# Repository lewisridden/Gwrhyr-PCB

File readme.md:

# PCB for Gwrhyr 
The flex PCB for Gwrhyr is forked from an improved variant of the BastardKB open-source manuform board, including the improvements for shape and access made by crystalhand.

The board has been modified in the following ways:
- Key footprints changed to Choc switches using the [reversible footprint by Keebio](https://github.com/keebio/Keebio-Parts.pretty/blob/master/Kailh-PG1350-1u-No-Clickhole.kicad_mod)
- Updated diode footprint to one from above Keebio library 
- Added HAT thumb cluster board
- Added board mount derived from [Swanmatch's ProMicro-Home](https://github.com/swanmatch/MxLEDBitPCB/tree/master/MxLEDBitPCB-promicro)

## License (inherited from fork)

Licensed under CC BY-NC-SA 4.0
Copyright Quentin Lebastard, Crystalhand, Swanmatch, Lewis Merriman

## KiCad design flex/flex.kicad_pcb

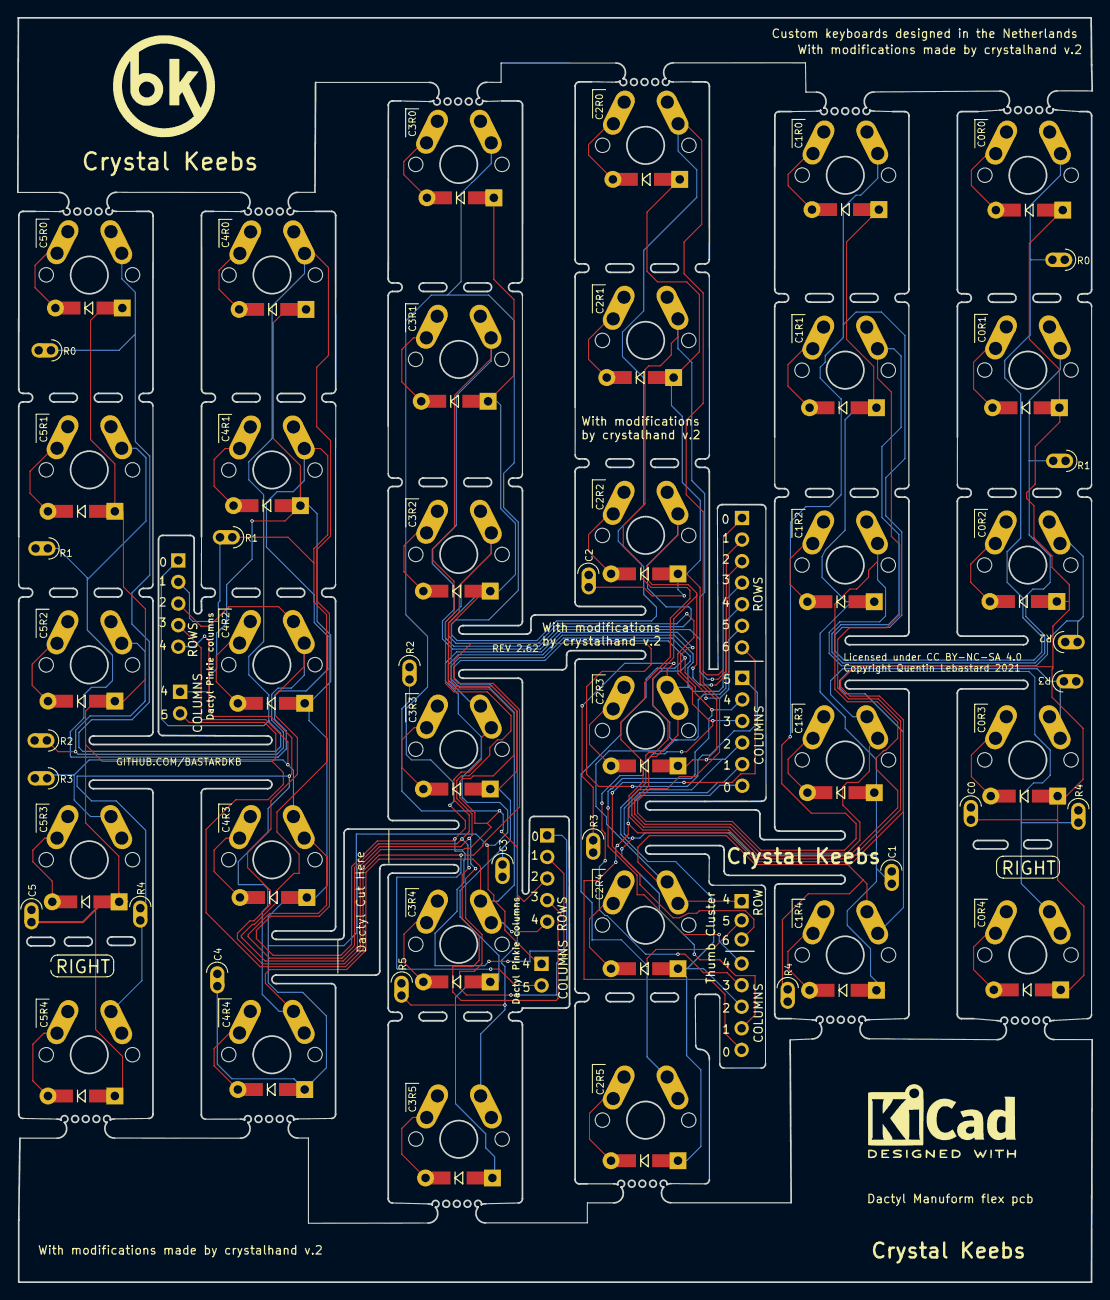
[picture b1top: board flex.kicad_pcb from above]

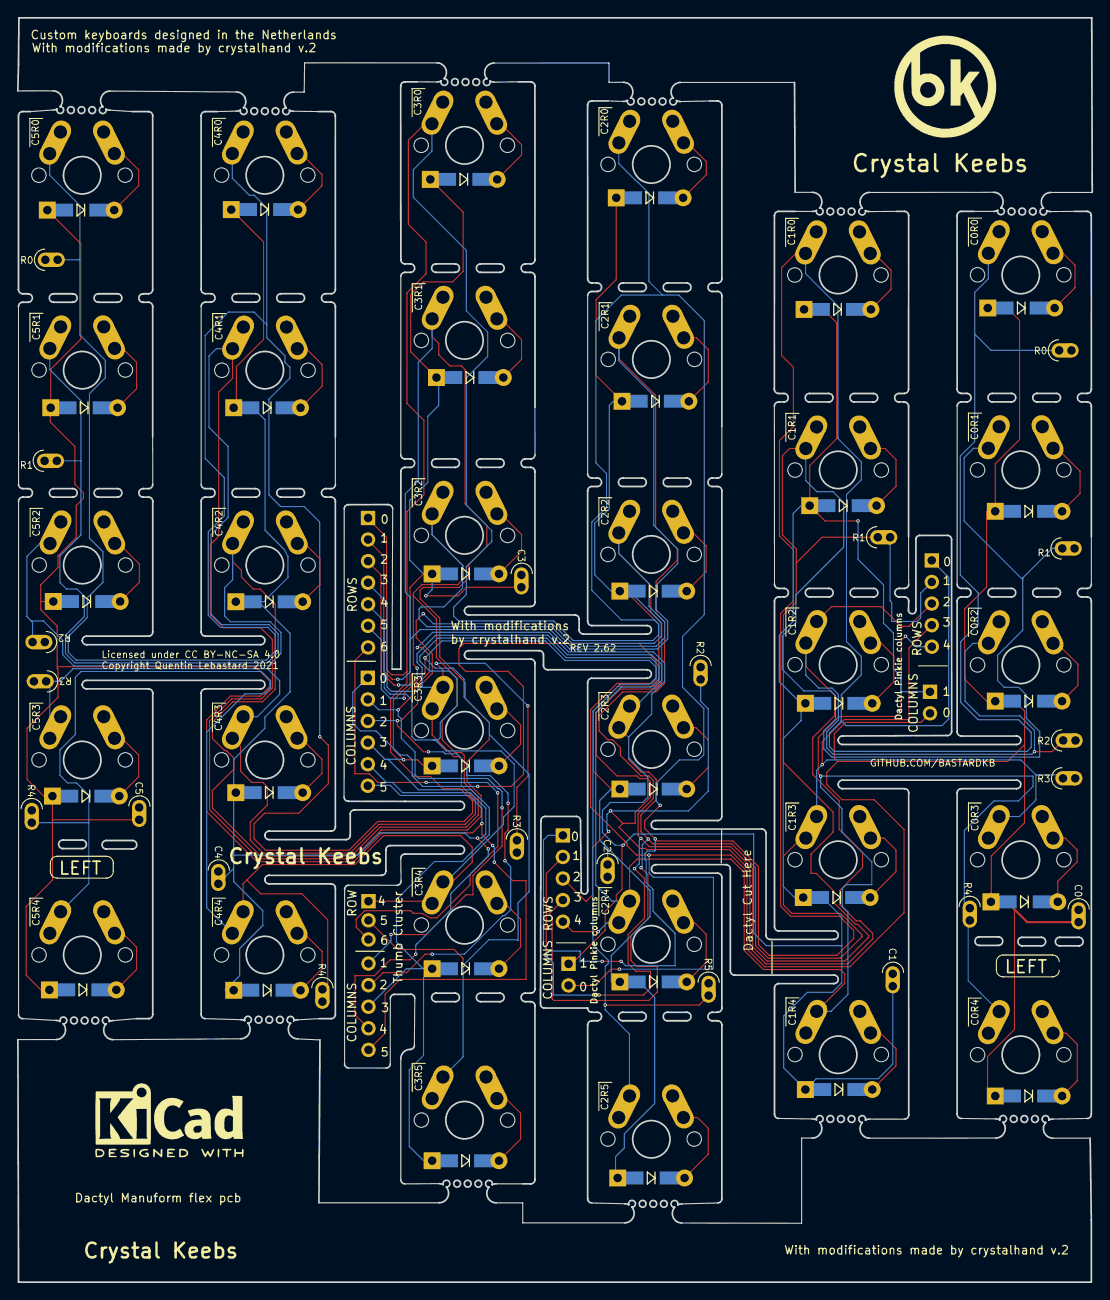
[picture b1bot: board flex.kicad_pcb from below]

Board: 2 copper layers, 126.5 x 148.8 mm, 92 parts (58 on the bottom side), 45 nets.

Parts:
D1, D2, D3, D4, D5, D6, D7, D8, D9, D10, D11, D12, D13, D14, D15, D16, D17, D18, D19, D20, D21, D22, D23, D24, D25, D26, D27, D28, D29, D30, D31, D32: D; Diode_TH_SOD123
J1: Conn_01x08_Female; PinSocket_1x06_P2.54mm_Vertical
J2, J2#2, J2#3: Conn_01x07_Female; PinSocket_1x07_P2.54mm_Vertical
J3, J3#2, J4, J4#2, J4#3, J5, J5#2, J5#3, J6, J6#2, J6#3, J7, J7#2, J7#3, J8, J9, J10, J11, J12, J13, J15: Conn_01x02_Female; SolderWire-0.15sqmm_1x01_D0.5mm_OD1.5mm
J14, J14#2, J14#3: Conn_01x06_Female; PinSocket_1x06_P2.54mm_Vertical
SW1, SW2, SW3, SW4, SW5, SW6, SW7, SW8, SW9, SW10, SW11, SW12, SW13, SW14, SW15, SW16, SW17, SW18, SW19, SW20, SW21, SW22, SW23, SW24, SW25, SW26, SW27, SW28, SW29, SW30, SW31, SW32: SW_Push; SW_MX_reversible

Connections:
unnamed: D1.2 (A), SW1.2
unnamed: D2.2 (A), SW2.2
unnamed: D3.2 (A), SW3.2
unnamed: D4.2 (A), SW4.2
unnamed: D5.2 (A), SW5.2
unnamed: D6.2 (A), SW6.2
unnamed: D7.2 (A), SW7.2
unnamed: D8.2 (A), SW8.2
unnamed: D9.2 (A), SW9.2
unnamed: D10.2 (A), SW10.2
unnamed: D11.2 (A), SW11.2
unnamed: D12.2 (A), SW12.2
unnamed: D13.2 (A), SW13.2
unnamed: D14.2 (A), SW14.2
unnamed: D15.2 (A), SW15.2
unnamed: D16.2 (A), SW16.2
unnamed: D17.2 (A), SW17.2
unnamed: D18.2 (A), SW18.2
unnamed: D19.2 (A), SW19.2
unnamed: D20.2 (A), SW20.2
unnamed: D21.2 (A), SW21.2
unnamed: D22.2 (A), SW22.2
unnamed: D23.2 (A), SW23.2
unnamed: D24.2 (A), SW24.2
unnamed: D25.2 (A), SW25.2
unnamed: D26.2 (A), SW26.2
unnamed: D27.2 (A), SW27.2
unnamed: D28.2 (A), SW28.2
unnamed: D29.2 (A), SW29.2
unnamed: D30.2 (A), SW30.2
unnamed: D31.2 (A), SW31.2
unnamed: D32.2 (A), SW32.2
col0: D1.1 (K), D2.1 (K), D3.1 (K), D4.1 (K), D27.1 (K), J9.1, J14.2, J14#2.2, J14#3.1
col1: D5.1 (K), D6.1 (K), D7.1 (K), D8.1 (K), D28.1 (K), J1.2, J10.1, J14.1, J14#2.1, J14#3.2
col2: D9.1 (K), D10.1 (K), D11.1 (K), D12.1 (K), D13.1 (K), D29.1 (K), J1.3, J11.1, J14#3.3
col3: D14.1 (K), D15.1 (K), D16.1 (K), D17.1 (K), D18.1 (K), D30.1 (K), J1.4, J12.1, J14#3.4
col4: D19.1 (K), D20.1 (K), D21.1 (K), D22.1 (K), D31.1 (K), J1.5, J13.1, J14#3.5
col5: D23.1 (K), D24.1 (K), D25.1 (K), D26.1 (K), D32.1 (K), J1.6, J14#3.6, J15.1
row0: J2.1, J2#2.1, J2#3.1, J3.1, J3#2.1, SW27.1, SW28.1, SW29.1, SW30.1, SW31.1, SW32.1
row1: J2.2, J2#2.2, J2#3.2, J4.1, J4#2.1, J4#3.1, SW1.1, SW5.1, SW9.1, SW14.1, SW19.1, SW23.1
row2: J2.3, J2#2.3, J2#3.3, J5.1, J5#2.1, J5#3.1, SW2.1, SW6.1, SW10.1, SW15.1, SW20.1, SW24.1
row3: J2.4, J2#2.4, J2#3.4, J6.1, J6#2.1, J6#3.1, SW3.1, SW7.1, SW11.1, SW16.1, SW21.1, SW25.1
row4: J1.0, J2.5, J2#2.5, J2#3.5, J7.1, J7#2.1, J7#3.1, SW4.1, SW8.1, SW12.1, SW17.1, SW22.1, SW26.1
row5: J1.1, J2.6, J8.1, SW13.1, SW18.1
row6: J1.1, J2.7

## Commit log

2022-10-30 small readme changes
    Added description in the readme file to show what has been changed
2023-04-27 Update readme.md
    cleaned up the description with changes
2024-12-10 Fixed inconsistent spelling of board name between repositories
2025-01-14 update scope (keeping inter-column spacing)

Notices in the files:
flex/flex.kicad_pcb:
Copyright Quentin Lebastard 2021
